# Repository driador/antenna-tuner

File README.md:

# 1500 W Automated Antenna Tuner

KF0OWR's homebuilt 1500 W remote balanced tuner for a doublet on 160–10 m. It uses a 34 µH
roller inductor, two vacuum capacitors and Tohtsu relays, and sits in a wall-mounted
16 × 16 × 24″ cabinet. The design log is the source of truth. Everything else in this repo
(CAD, drawings, NEC models, KiCad boards) supports it, and the log cites these files by their
repo paths.

## Layout

| Path | Contents |
|---|---|
| `doc/design-log.md` | **Design log** (current revision in its header). §9 is the open-item list; §11 holds superseded designs |
| `doc/design-review-rev3.2.md` | Independent design review of Rev 3.2 and its dispositions |
| `doc/vacuum-cap-testing.md` | Bench procedure for the used vacuum capacitors |
| `doc/bench-tests.md` | Bench tests that retire the build risks before the enclosure is cut: the roller (L, idle-turn resonance, torque, contact heat, Q), K1 and K2 at full power, the AD8302 sign probe, and the 160 m decision if Q is low |
| `doc/diagrams/` | Graphviz sources (`*.dot`) and the rendered SVGs the log embeds |
| `doc/*.pdf` | Built log and review PDFs, plus a reference worksheet |
| `cad/` | build123d models (roller, enclosure, harness) and FreeCAD TechDraw sheet generators |
| `cad/out/*.pdf` | Drawing sheets: `L-100…109` roller, `E-200…219` enclosure, populated cabinet and harness |
| `nec/` | nec2++ and Python analyses: capacitor and inductor demand, roller and choke sweeps, tuning time, the general rating |
| `nec/out/*.csv`, `*.txt` | Analysis summaries the log quotes |
| `nec/data/` | Fair-Rite #61 material data (complex permeability, Pv vs B); Fair-Rite's, not under the project licenses |
| `kicad/` | Control and measurement boards, generated from Python (schematic → netlist → PCB → freerouting → DRC, `route.sh`); fab zip from `fab.sh` |
| `fw/` | Firmware: the portable C++17 core (tuning state machine, solver, bridge math, fault policy, motion planning) with its closed-loop host tests, and the Teensy 4.1 layer (PlatformIO); see `fw/README.md` |
| `host/` | The bench PC's tools: the CAT bridge (band-follow and one-button tune through Hamlib or flrig) and the firmware update over the network; see `host/README.md` |
| `LICENSE`, `NOTICE` | The CERN-OHL-W v2 text for the hardware and design; what each license covers, the notices and the third-party files (the firmware's GPL text is `fw/LICENSE`) |
| `archive/` | Early drafts and the Rev 3.3 / 3.4 log snapshots the log cites |

## Toolchain

| Area | Needs |
|---|---|
| Log / review PDF | `pandoc`, `weasyprint`, `poppler` (`pdftocairo`, `pdfinfo`), `python3`; `graphviz` only to re-render a diagram |
| CAD | Python 3.12 venv with `cad/requirements.txt` (build123d 0.13); FreeCAD 1.1 plus `xvfb-run` for the sheets |
| NEC | `nec2++` built statically at `~/src/necpp/build/src/nec2++` (scripts call that path); Python 3 stdlib only |
| KiCad | KiCad 10 (`kicad-cli`, `pcbnew` Python module), Java 25 and freerouting (`kicad/route.sh`) |
| Firmware | CMake ≥ 3.16 and a C++17 compiler for the host build and tests; PlatformIO for the Teensy build (it fetches PJRC's ARM toolchain and the QNEthernet library); `python3` to regenerate its tables |

Set up the CAD environment:

```bash
uv venv cad/.venv --python 3.12
uv pip install --python cad/.venv/bin/python -r cad/requirements.txt
```

Build `nec2++` (the shared-library build breaks once `libnecpp.so` goes missing, so use the static build):

```bash
git clone https://github.com/tmolteno/necpp ~/src/necpp
cmake -S ~/src/necpp -B ~/src/necpp/build -DBUILD_SHARED_LIBS=OFF -DCMAKE_BUILD_TYPE=Release
cmake --build ~/src/necpp/build -j
```

## Build order

When the geometry changes, regenerate the CAD and sheets **in this order**, then rebuild the log
so appendices A/B pick up the new sheets:

```bash
cd cad
.venv/bin/python roller.py          # roller model + interference check
.venv/bin/python enclosure.py       # cabinet, panels, fixtures + interference check
.venv/bin/python harness.py         # color-coded wire runs + clearance check
.venv/bin/python svgviews.py        # hidden-line SVG views used by the sheets
timeout 900 xvfb-run -a freecad drawings.py             # L-100…109
timeout 900 xvfb-run -a freecad drawings_enclosure.py   # E-200…219
cd ../doc && ./build.sh             # → doc/tuner-design-log.pdf
```

The panel sheets place each cutout by ordinates from the panel's lower-left corner and label it with its
size. `cad/ordinate.py` lays these out as an SVG overlay on each view, and it needs no FreeCAD:
`python3 ordinate.py /tmp/out` writes every panel's overlay, so a layout can be checked quickly.

Always wrap the FreeCAD runs in `timeout`. A module-level exception in a sheet script leaves
FreeCAD hanging under xvfb with an empty log. Re-render a diagram with
`dot -Tsvg doc/diagrams/X.dot -o doc/diagrams/X.svg`. The review builds with `doc/build_review.sh`.

## What is tracked

- **Git LFS** (`.gitattributes`) holds every `*.pdf`, `*.png` and `*.jpg`: drawing sheets, built
  PDFs, KiCad plots and references. Run `git lfs install --local` after cloning.
- **Not tracked** (`.gitignore`) are outputs the scripts regenerate wholesale on every run:
  - STEP models and FreeCAD documents
  - sheet SVGs and logs in `cad/out/`
  - raw NEC decks and solver output (`nec/out/*.nec`, `*.out`, about 420 MB)
  - the HTML intermediates and `doc/sheets/`
  - the firmware builds, `fw/build/` and `fw/.pio/`
  - the venv
  - `.*.pre-*` working backups, since git history replaces them
- The summaries that analyses produce (`nec/out/*.csv`, `*.txt`, `nec/cap_demand_rev37b.out`)
  **are** tracked, because the log quotes them.

## License

This is open hardware. The boards, CAD, drawings, NEC models and the design log are licensed under
the [CERN-OHL-W v2](LICENSE), and the firmware in `fw/` and the bench PC's tools in `host/` under
the [GPL v3 or later](fw/LICENSE). [`NOTICE`](NOTICE) has the details, including
the third-party files. Source location: <https://github.com/driador/antenna-tuner>.

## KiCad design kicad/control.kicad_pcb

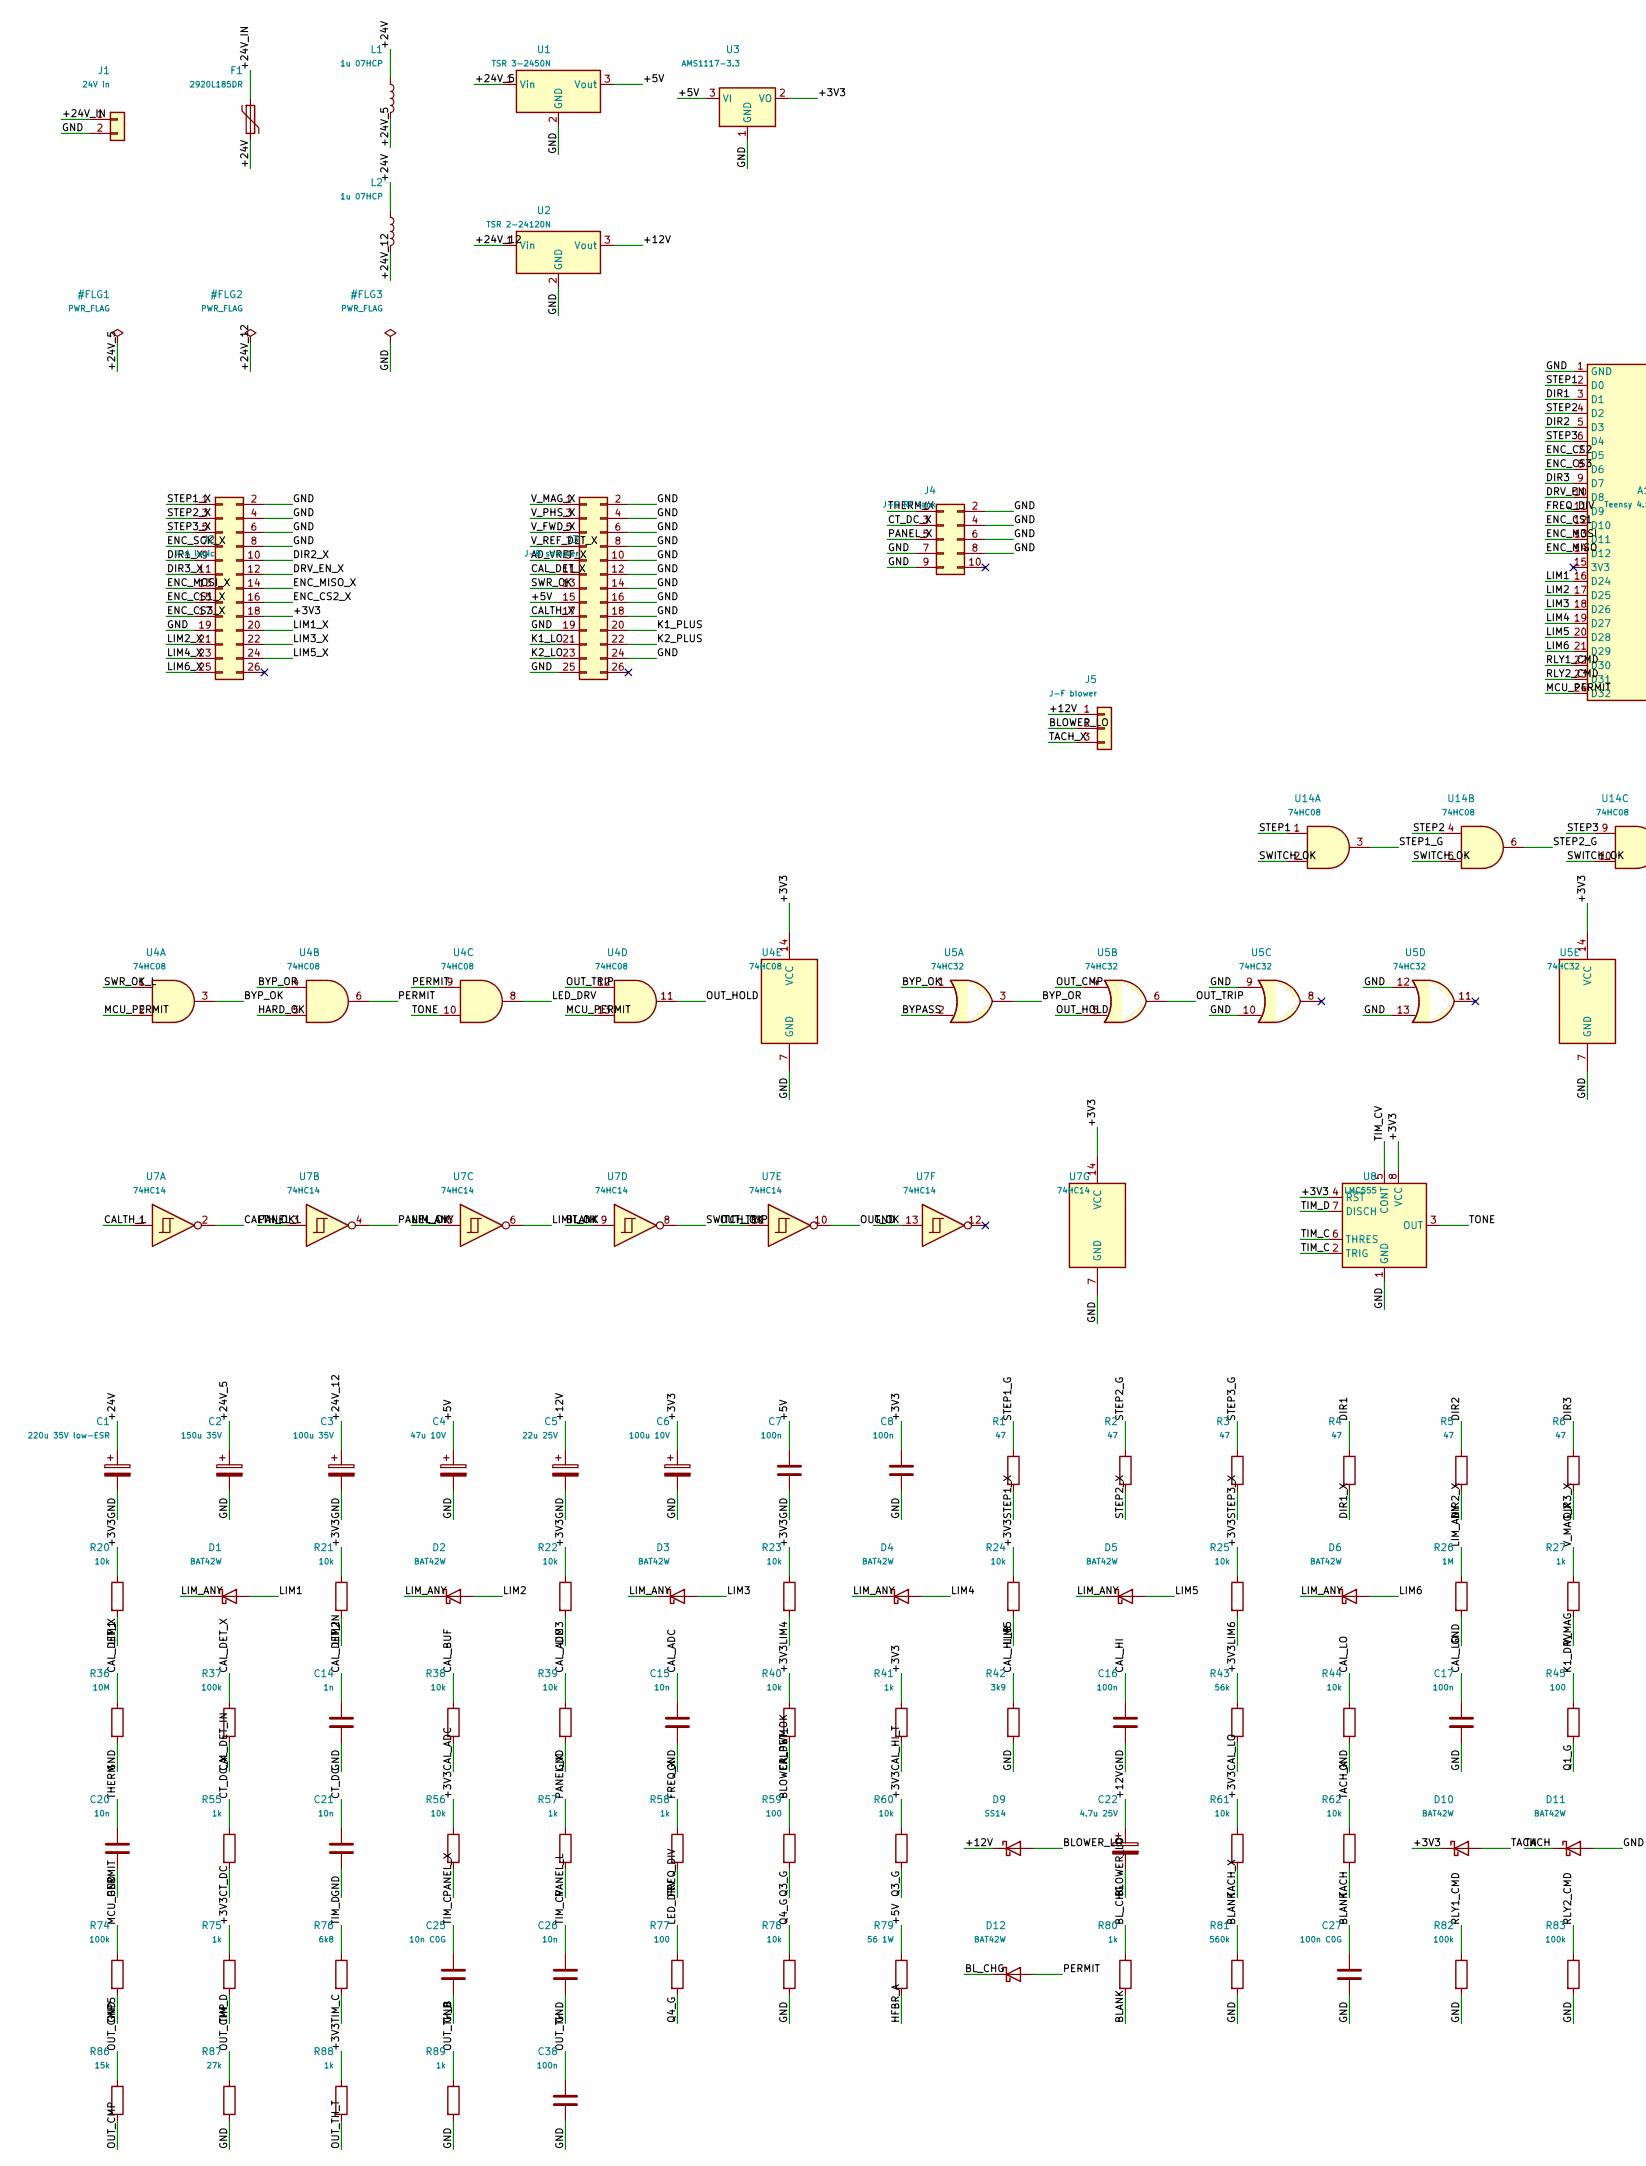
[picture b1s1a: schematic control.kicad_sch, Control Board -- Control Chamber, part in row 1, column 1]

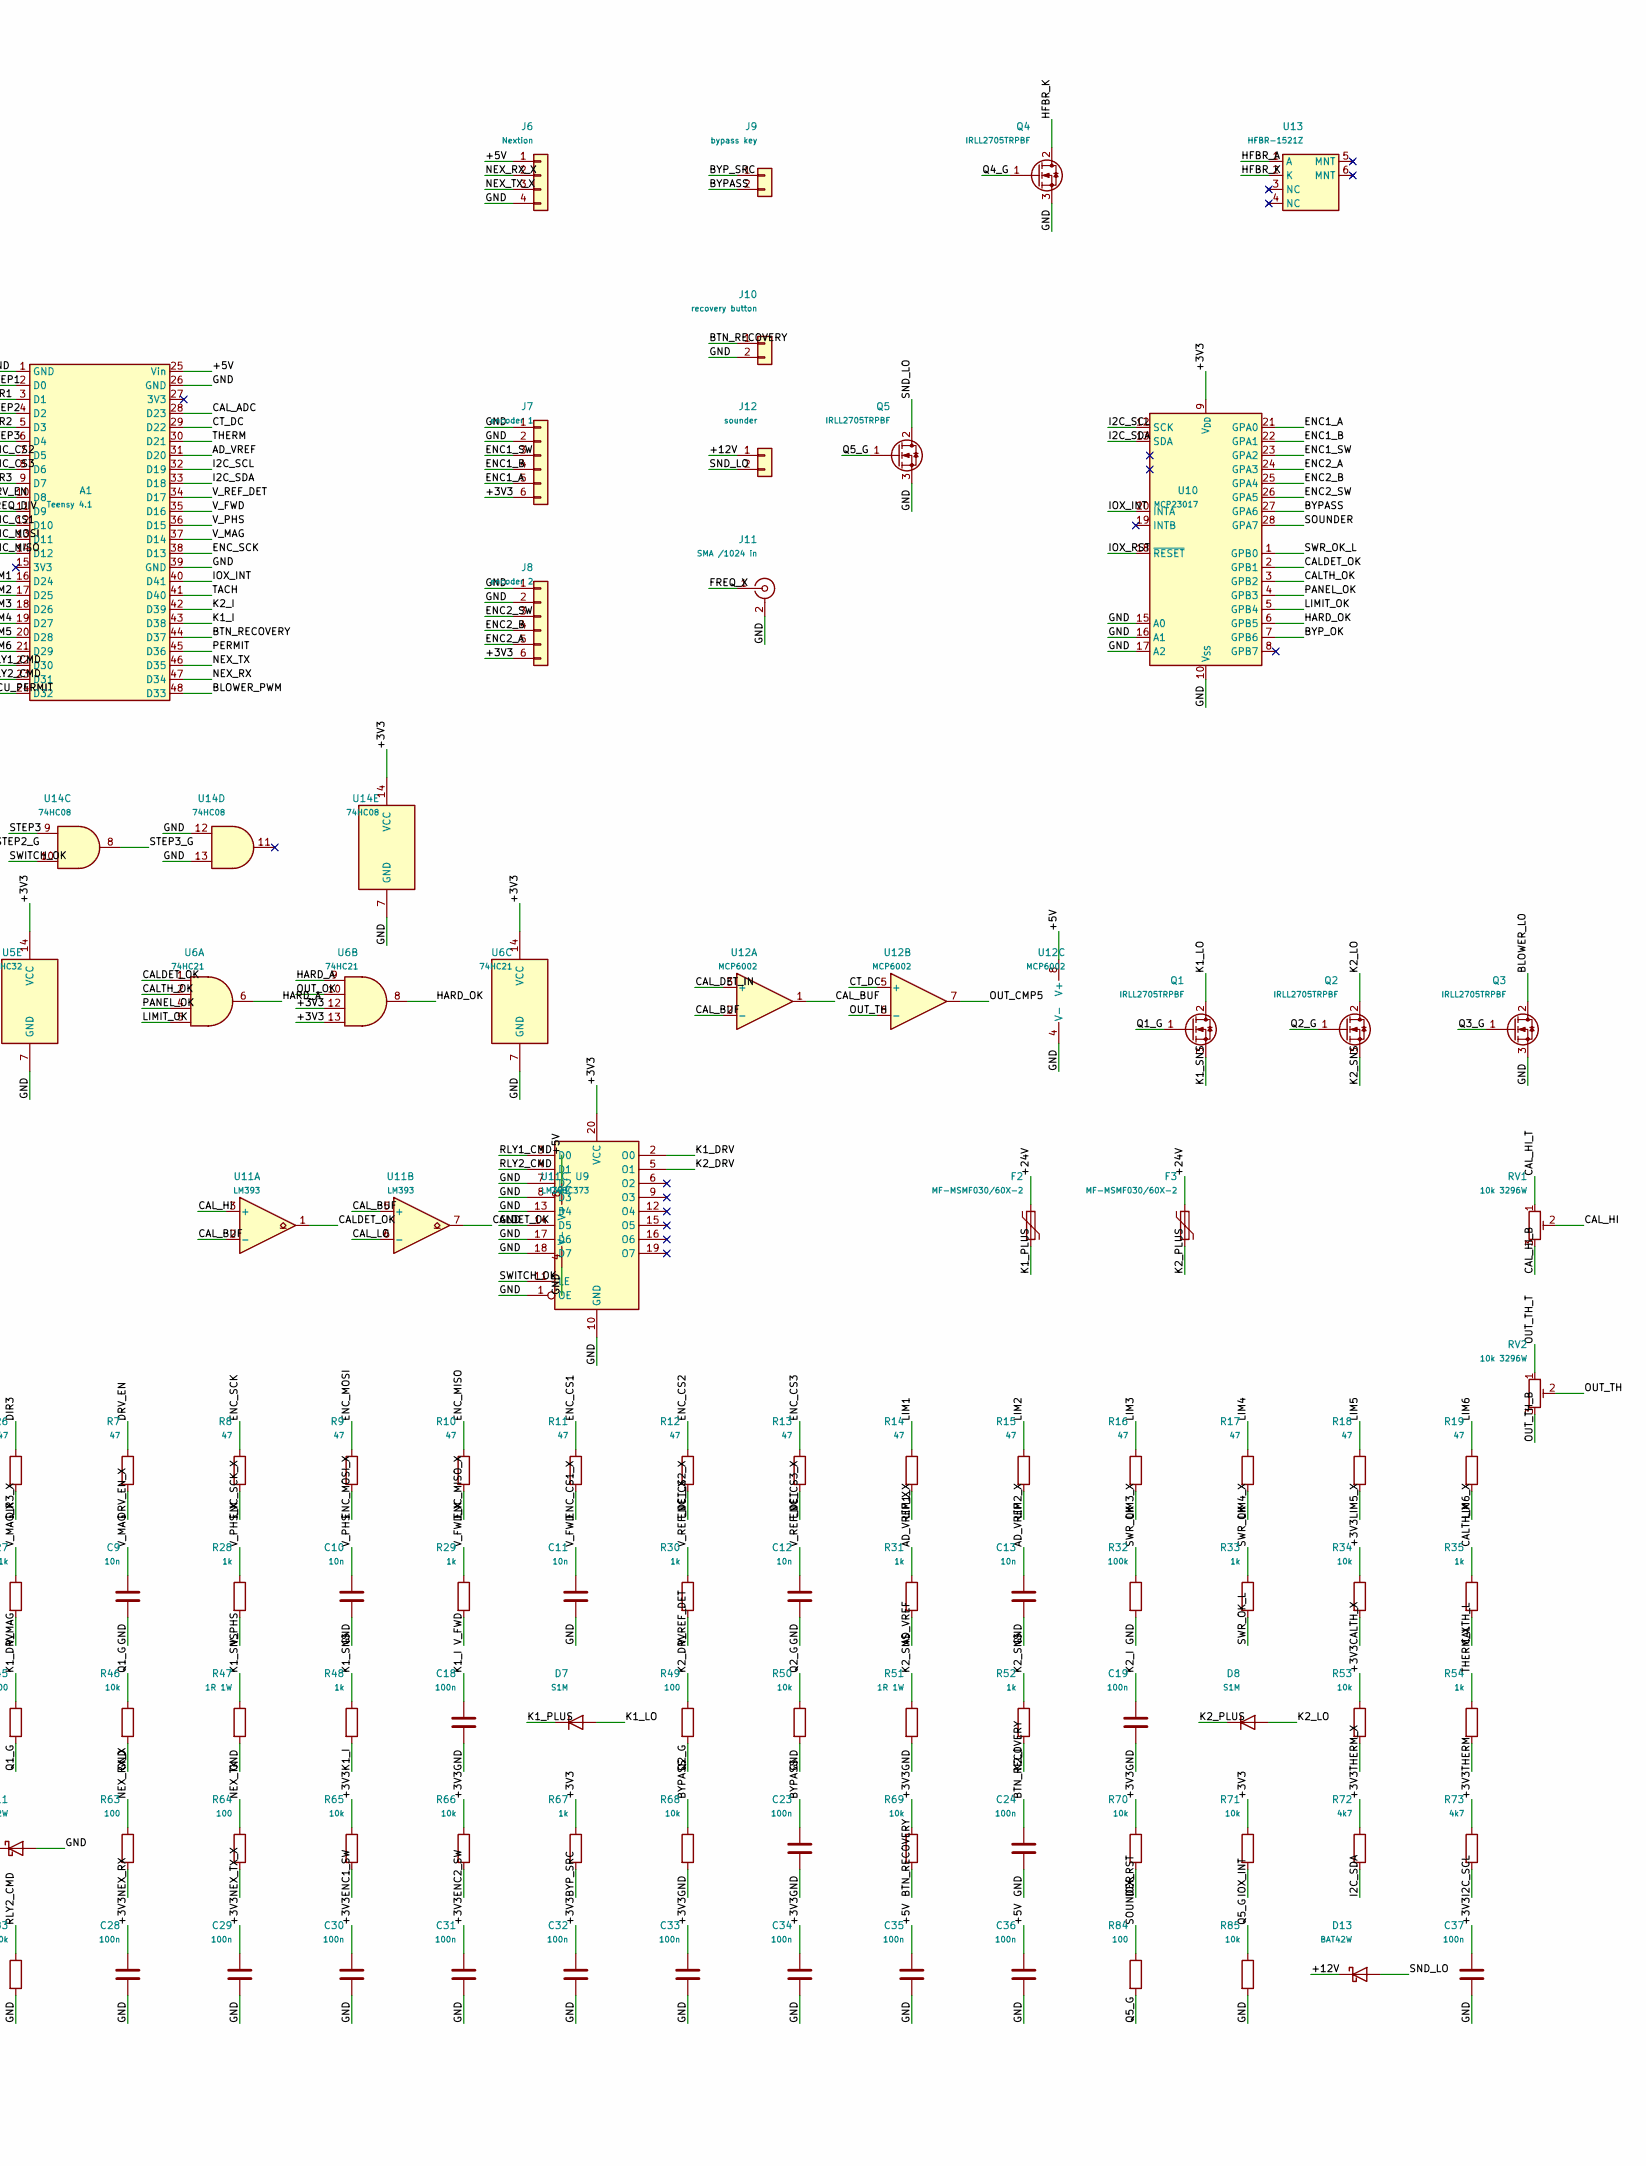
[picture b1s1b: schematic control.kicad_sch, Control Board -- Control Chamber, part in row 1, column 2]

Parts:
A1: Teensy 4.1; Teensy4.1
C1: 220u 35V low-ESR; CP_Radial_D8.0mm_P3.50mm
C2: 150u 35V; CP_Radial_D8.0mm_P3.50mm
C3: 100u 35V; CP_Radial_D6.3mm_P2.50mm
C4: 47u 10V; CP_Radial_D5.0mm_P2.50mm
C5: 22u 25V; CP_Radial_D5.0mm_P2.50mm
C6: 100u 10V; CP_Radial_D6.3mm_P2.50mm
C7, C8, C16, C17, C18, C19, C23, C24, C28, C29, C30, C31, C32, C33, C34, C35, C36, C37, C38: 100n; C_1206_3216Metric
C9, C10, C11, C12, C13, C15, C20, C21, C26: 10n; C_1206_3216Metric
C14: 1n; C_1206_3216Metric
C22: 4.7u 25V; CP_Radial_D5.0mm_P2.50mm
C25: 10n C0G; C_1206_3216Metric
C27: 100n C0G; C_1206_3216Metric
D1, D2, D3, D4, D5, D6, D10, D11, D12, D13: BAT42W; D_SOD-123
D7, D8: S1M; D_SMA
D9: SS14; D_SMA
F1: 2920L185DR; Fuse_2920_7451Metric
F2, F3: MF-MSMF030/60X-2; Fuse_1812_4532Metric
J1: 24V in; TerminalBlock_Phoenix_MKDS-1,5-2-5.08_1x02_P5.08mm_Horizont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
J2: J-A logic; IDC-Header_2x13_P2.54mm_Vertical
J3: J-B sampler; IDC-Header_2x13_P2.54mm_Vertical
J4: J-E RF tank; IDC-Header_2x05_P2.54mm_Vertical
J5: J-F blower; PinHeader_1x03_P2.54mm_Vertical
J6: Nextion; PinHeader_1x04_P2.54mm_Vertical
J7: encoder 1; PinHeader_1x06_P2.54mm_Vertical
J8: encoder 2; PinHeader_1x06_P2.54mm_Vertical
J9: bypass key; PinHeader_1x02_P2.54mm_Vertical
J10: recovery button; PinHeader_1x02_P2.54mm_Vertical
J11: SMA /1024 in; SMA_Amphenol_132134-11_Vertical
J12: sounder; PinHeader_1x02_P2.54mm_Vertical
L1, L2: 1u 07HCP; L_Radial_D7.8mm_P5.00mm_Fastron_07HCP
Q1, Q2, Q3, Q4, Q5: IRLL2705TRPBF; SOT-223-3_TabPin2
R1, R2, R3, R4, R5, R6, R7, R8, R9, R10, R11, R12, R13, R14, R15, R16, R17, R18, R19: 47; R_1206_3216Metric
R20, R21, R22, R23, R24, R25, R34, R38, R39, R40, R44, R46, R50, R53, R56, R60, R61, R62, R65, R66, R68, R69, R70, R71, R78, R85: 10k; R_1206_3216Metric
R26: 1M; R_1206_3216Metric
R27, R28, R29, R30, R31, R33, R35, R41, R48, R52, R54, R55, R57, R58, R67, R75, R80, R88, R89: 1k; R_1206_3216Metric
R32, R37, R74, R82, R83: 100k; R_1206_3216Metric
R36: 10M; R_1206_3216Metric
R42: 3k9; R_1206_3216Metric
R43: 56k; R_1206_3216Metric
R45, R49, R59, R63, R64, R77, R84: 100; R_1206_3216Metric
R47, R51: 1R 1W; R_2512_6332Metric
R72, R73: 4k7; R_1206_3216Metric
R76: 6k8; R_1206_3216Metric
R79: 56 1W; R_2512_6332Metric
R81: 560k; R_1206_3216Metric
R86: 15k; R_1206_3216Metric
R87: 27k; R_1206_3216Metric
RV1, RV2: 10k 3296W; Potentiometer_Bourns_3296W_Vertical
U1: TSR 3-2450N; Converter_DCDC_TRACO_TSR2-24xxN_TSR2-24xxxN_THT
U2: TSR 2-24120N; Converter_DCDC_TRACO_TSR2-24xxN_TSR2-24xxxN_THT
U3: AMS1117-3.3; SOT-223-3_TabPin2
U4, U14: 74HC08; SOIC-14_3.9x8.7mm_P1.27mm
U5: 74HC32; SOIC-14_3.9x8.7mm_P1.27mm
U6: 74HC21; SOIC-14_3.9x8.7mm_P1.27mm
U7: 74HC14; SOIC-14_3.9x8.7mm_P1.27mm
U8: LMC555; SOIC-8_3.9x4.9mm_P1.27mm
U9: 74HC373; SOIC-20W_7.5x12.8mm_P1.27mm
U10: MCP23017; SOIC-28W_7.5x17.9mm_P1.27mm
U11: LM393; SOIC-8_3.9x4.9mm_P1.27mm
U12: MCP6002; SOIC-8_3.9x4.9mm_P1.27mm
U13: HFBR-1521Z; AGILENT_HFBR-152x

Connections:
+3V3: C6.1, C8.1, C28.1, C29.1, C30.1, C31.1, C32.1, C33.1, C34.1, C37.1, D10.1 (K), J2.18, J7.6, J8.6, R20.1, R21.1, R22.1, R23.1, R24.1, R25.1, R34.1, R40.1, R41.1, R43.1, R53.1, R56.1, R60.1, R61.1, R65.1, R66.1, R67.1, R69.1, R70.1, R71.1, R72.1, R73.1, R75.1, R88.1, U3.2 (VO), U4.14 (VCC), U5.14 (VCC), U6.12, U6.13, U6.14 (VCC), U7.14 (VCC), U8.4 (~RST), U8.8 (VCC), U9.20 (VCC), U10.9 (V_{DD}), U14.14 (VCC)
+5V: A1.25 (Vin), C4.1, C7.1, C35.1, C36.1, J3.15, J6.1, R79.1, U1.3 (Vout), U3.3 (VI), U11.8 (V+), U12.8 (V+)
+12V: C5.1, C22.1, D9.1 (K), D13.1 (K), J5.1, J12.1, U2.3 (Vout)
+24V: C1.1, F1.2, F2.1, F3.1, L1.1, L2.1
+24V_5: C2.1, L1.2, U1.1 (Vin)
+24V_12: C3.1, L2.2, U2.1 (Vin)
+24V_IN: F1.1, J1.1
AD_VREF: A1.31 (20), C13.1, R31.2
AD_VREF_X: J3.9, R31.1
BLANK: C27.1, R80.2, R81.1, U7.9
BLOWER_LO: C22.2, D9.2 (A), J5.2, Q3.2 (D)
BLOWER_PWM: A1.48 (33), R59.1
BL_CHG: D12.1 (K), R80.1
BTN_RECOVERY: A1.44 (37), C24.1, J10.1, R69.2
BYPASS: C23.1, J9.2, R68.1, U5.2, U10.27 (GPA6)
BYP_OK: U4.3, U5.1, U10.7 (GPB6)
BYP_OR: U4.4, U5.3
BYP_SRC: J9.1, R67.2
CALDET_OK: R40.2, U6.1, U10.2 (GPB1), U11.1, U11.7
CALTH_L: R35.2, U7.1
CALTH_OK: U6.2, U7.2, U10.3 (GPB2)
CALTH_X: J3.17, R34.2, R35.1
CAL_ADC: A1.28 (23), C15.1, R38.2, R39.1
CAL_BUF: R38.1, U11.2 (-), U11.5 (+), U12.1, U12.2 (-)
CAL_DET_IN: C14.1, R37.2, U12.3 (+)
CAL_DET_X: J3.11, R36.1, R37.1
CAL_HI: C16.1, RV1.2, U11.3 (+)
CAL_HI_B: R42.1, RV1.3
CAL_HI_T: R41.2, RV1.1
CAL_LO: C17.1, R43.2, R44.1, U11.6 (-)
CT_DC: A1.29 (22), C21.1, R55.2, U12.5 (+)
CT_DC_X: J4.3, R55.1
DIR1: A1.3 (1), R4.1
DIR1_X: J2.9, R4.2
DIR2: A1.5 (3), R5.1
DIR2_X: J2.10, R5.2
DIR3: A1.9 (7), R6.1
DIR3_X: J2.11, R6.2
DRV_EN: A1.10 (8), R7.1
DRV_EN_X: J2.12, R7.2
ENC1_A: J7.5, U10.21 (GPA0)
ENC1_B: J7.4, U10.22 (GPA1)
ENC1_SW: J7.3, R65.2, U10.23 (GPA2)
ENC2_A: J8.5, U10.24 (GPA3)
ENC2_B: J8.4, U10.25 (GPA4)
ENC2_SW: J8.3, R66.2, U10.26 (GPA5)
ENC_CS1: A1.12 (10), R11.1
ENC_CS1_X: J2.15, R11.2
ENC_CS2: A1.7 (5), R12.1
ENC_CS2_X: J2.16, R12.2
ENC_CS3: A1.8 (6), R13.1
ENC_CS3_X: J2.17, R13.2
ENC_MISO: A1.14 (12), R10.1
ENC_MISO_X: J2.14, R10.2
ENC_MOSI: A1.13 (11), R9.1
ENC_MOSI_X: J2.13, R9.2
ENC_SCK: A1.38 (13), R8.1
ENC_SCK_X: J2.7, R8.2
FREQ_DIV: A1.11 (9), R58.2
FREQ_X: J11.1 (In), R58.1
GND: A1.1 (GND), A1.26 (GND), A1.39 (GND), C1.2, C2.2, C3.2, C4.2, C5.2, C6.2, C7.2, C8.2, C9.2, C10.2, C11.2, C12.2, C13.2, C14.2, C15.2, C16.2, C17.2, C18.2, C19.2, C20.2, C21.2, C23.2, C24.2, C25.2, C26.2, C27.2, C28.2, C29.2, C30.2, C31.2, C32.2, C33.2, C34.2, C35.2, C36.2, C37.2, C38.2, D11.2 (A), J1.2, J2.2, J2.4, J2.6, J2.8, J2.19, J3.2, J3.4, J3.6, J3.8, J3.10, J3.12, J3.14, J3.16, J3.18, J3.19, J3.24, J3.25, J4.2, J4.4, J4.6, J4.7, J4.8, J4.9, J6.4, J7.1, J7.2, J8.1, J8.2, J10.2, J11.2 (Ext), Q3.3 (S), Q4.3 (S), Q5.3 (S), R26.2, R32.2, R36.2, R39.2, R42.2, R44.2, R46.2, R47.2, R50.2, R51.2, R68.2, R74.2, R78.2, R81.2, R82.2, R83.2, R85.2, R87.2, R89.2, U1.2 (GND), U2.2 (GND), U3.1 (GND), U4.7 (GND), U5.7 (GND), U5.9, U5.10, U5.12, U5.13, U6.7 (GND), U7.7 (GND), U7.13, U8.1 (GND), U9.1 (OE), U9.7 (D2), U9.8 (D3), U9.10 (GND), U9.13 (D4), U9.14 (D5), U9.17 (D6), U9.18 (D7), U10.10 (V_{SS}), U10.15 (A0), U10.16 (A1), U10.17 (A2), U11.4 (V-), U12.4 (V-), U14.7 (GND), U14.12, U14.13
HARD_A: U6.6, U6.9
HARD_OK: U4.5, U6.8, U10.6 (GPB5)
HFBR_A: R79.2, U13.1 (A)
HFBR_K: Q4.2 (D), U13.2 (K)
I2C_SCL: A1.32 (19), R73.2, U10.12 (SCK)
I2C_SDA: A1.33 (18), R72.2, U10.13 (SDA)
IOX_INT: A1.40 (41), R71.2, U10.20 (INTA)
IOX_RST: R70.2, U10.18 (~RESET)
K1_DRV: R45.1, U9.2 (O0)
K1_I: A1.43 (38), C18.1, R48.2
K1_LO: D7.2 (A), J3.21, Q1.2 (D)
K1_PLUS: D7.1 (K), F2.2, J3.20
K1_SNS: Q1.3 (S), R47.1, R48.1
K2_DRV: R49.1, U9.5 (O1)
K2_I: A1.42 (39), C19.1, R52.2
K2_LO: D8.2 (A), J3.23, Q2.2 (D)
K2_PLUS: D8.1 (K), F3.2, J3.22
K2_SNS: Q2.3 (S), R51.1, R52.1
LED_DRV: R77.1, U4.8
LIM1: A1.16 (24), D1.2 (A), R14.1, R20.2
LIM1_X: J2.20, R14.2
LIM2: A1.17 (25), D2.2 (A), R15.1, R21.2
LIM2_X: J2.21, R15.2
LIM3: A1.18 (26), D3.2 (A), R16.1, R22.2
LIM3_X: J2.22, R16.2
LIM4: A1.19 (27), D4.2 (A), R17.1, R23.2
LIM4_X: J2.23, R17.2
LIM5: A1.20 (28), D5.2 (A), R18.1, R24.2
LIM5_X: J2.24, R18.2
LIM6: A1.21 (29), D6.2 (A), R19.1, R25.2
LIM6_X: J2.25, R19.2
LIMIT_OK: U6.5, U7.6, U10.5 (GPB4)
LIM_ANY: D1.1 (K), D2.1 (K), D3.1 (K), D4.1 (K), D5.1 (K), D6.1 (K), R26.1, U7.5
MCU_PERMIT: A1.24 (32), R74.1, U4.2, U4.13
NEX_RX: A1.47 (34), R63.2
NEX_RX_X: J6.2, R63.1
NEX_TX: A1.46 (35), R64.1
NEX_TX_X: J6.3, R64.2
OUT_CMP: R86.2, R87.1, U5.4
OUT_CMP5: R86.1, U12.7
OUT_HOLD: U4.11, U5.5
OUT_OK: U6.10, U7.10
OUT_TH: C38.1, RV2.2, U12.6 (-)
OUT_TH_B: R89.1, RV2.3
OUT_TH_T: R88.2, RV2.1
OUT_TRIP: U4.12, U5.6, U7.11
PANEL_L: R57.2, U7.3
PANEL_OK: U6.4, U7.4, U10.4 (GPB3)
PANEL_X: J4.5, R56.2, R57.1
PERMIT: A1.45 (36), D12.2 (A), U4.6, U4.9
Q1_G: Q1.1 (G), R45.2, R46.1
Q2_G: Q2.1 (G), R49.2, R50.1
Q3_G: Q3.1 (G), R59.2, R60.2
Q4_G: Q4.1 (G), R77.2, R78.1
Q5_G: Q5.1 (G), R84.2, R85.1
RLY1_CMD: A1.22 (30), R82.1, U9.3 (D0)
RLY2_CMD: A1.23 (31), R83.1, U9.4 (D1)
SND_LO: D13.2 (A), J12.2, Q5.2 (D)
SOUNDER: R84.1, U10.28 (GPA7)
STEP1: A1.2 (0), U14.1
STEP1_G: R1.1, U14.3
STEP1_X: J2.1, R1.2
STEP2: A1.4 (2), U14.4
STEP2_G: R2.1, U14.6
STEP2_X: J2.3, R2.2
STEP3: A1.6 (4), U14.9
STEP3_G: R3.1, U14.8
STEP3_X: J2.5, R3.2
SWITCH_OK: U7.8, U9.11 (LE), U14.2, U14.5, U14.10
SWR_OK: J3.13, R32.1, R33.1
SWR_OK_L: R33.2, U4.1, U10.1 (GPB0)
TACH: A1.41 (40), D10.2 (A), D11.1 (K), R62.2
TACH_X: J5.3, R61.2, R62.1
THERM: A1.30 (21), C20.1, R54.2
THERM_X: J4.1, R53.2, R54.1
TIM_C: C25.1, R76.2, U8.2 (TRIG), U8.6 (THRES)
TIM_CV: C26.1, U8.5 (CONT)
TIM_D: R75.2, R76.1, U8.7 (DISCH)
TONE: U4.10, U8.3 (OUT)
V_FWD: A1.35 (16), C11.1, R29.2
V_FWD_X: J3.5, R29.1
V_MAG: A1.37 (14), C9.1, R27.2
V_MAG_X: J3.1, R27.1
V_PHS: A1.36 (15), C10.1, R28.2
V_PHS_X: J3.3, R28.1
V_REF_DET: A1.34 (17), C12.1, R30.2
V_REF_DET_X: J3.7, R30.1

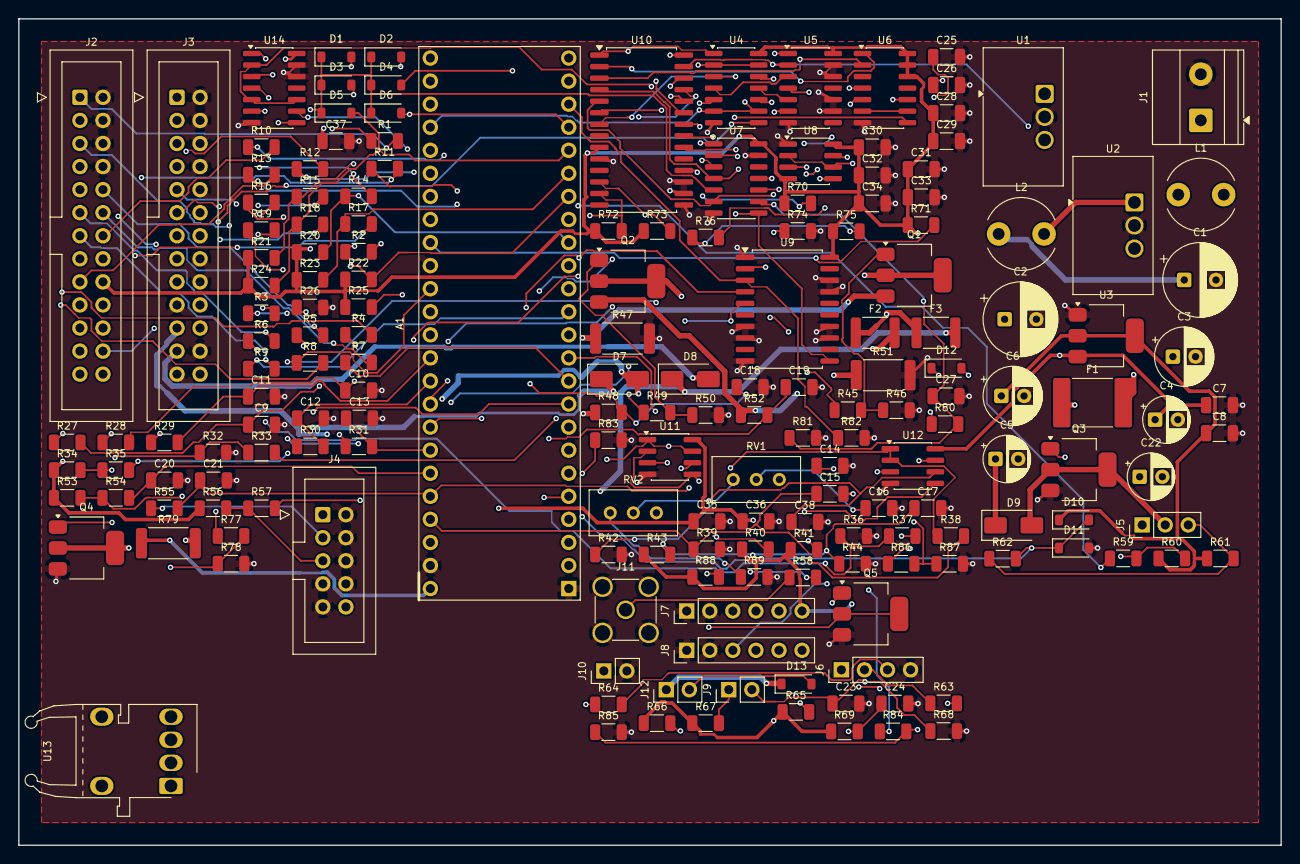
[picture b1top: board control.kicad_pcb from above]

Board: 4 copper layers, 139.0 x 91.0 mm, 179 parts (0 on the bottom side), 148 nets.

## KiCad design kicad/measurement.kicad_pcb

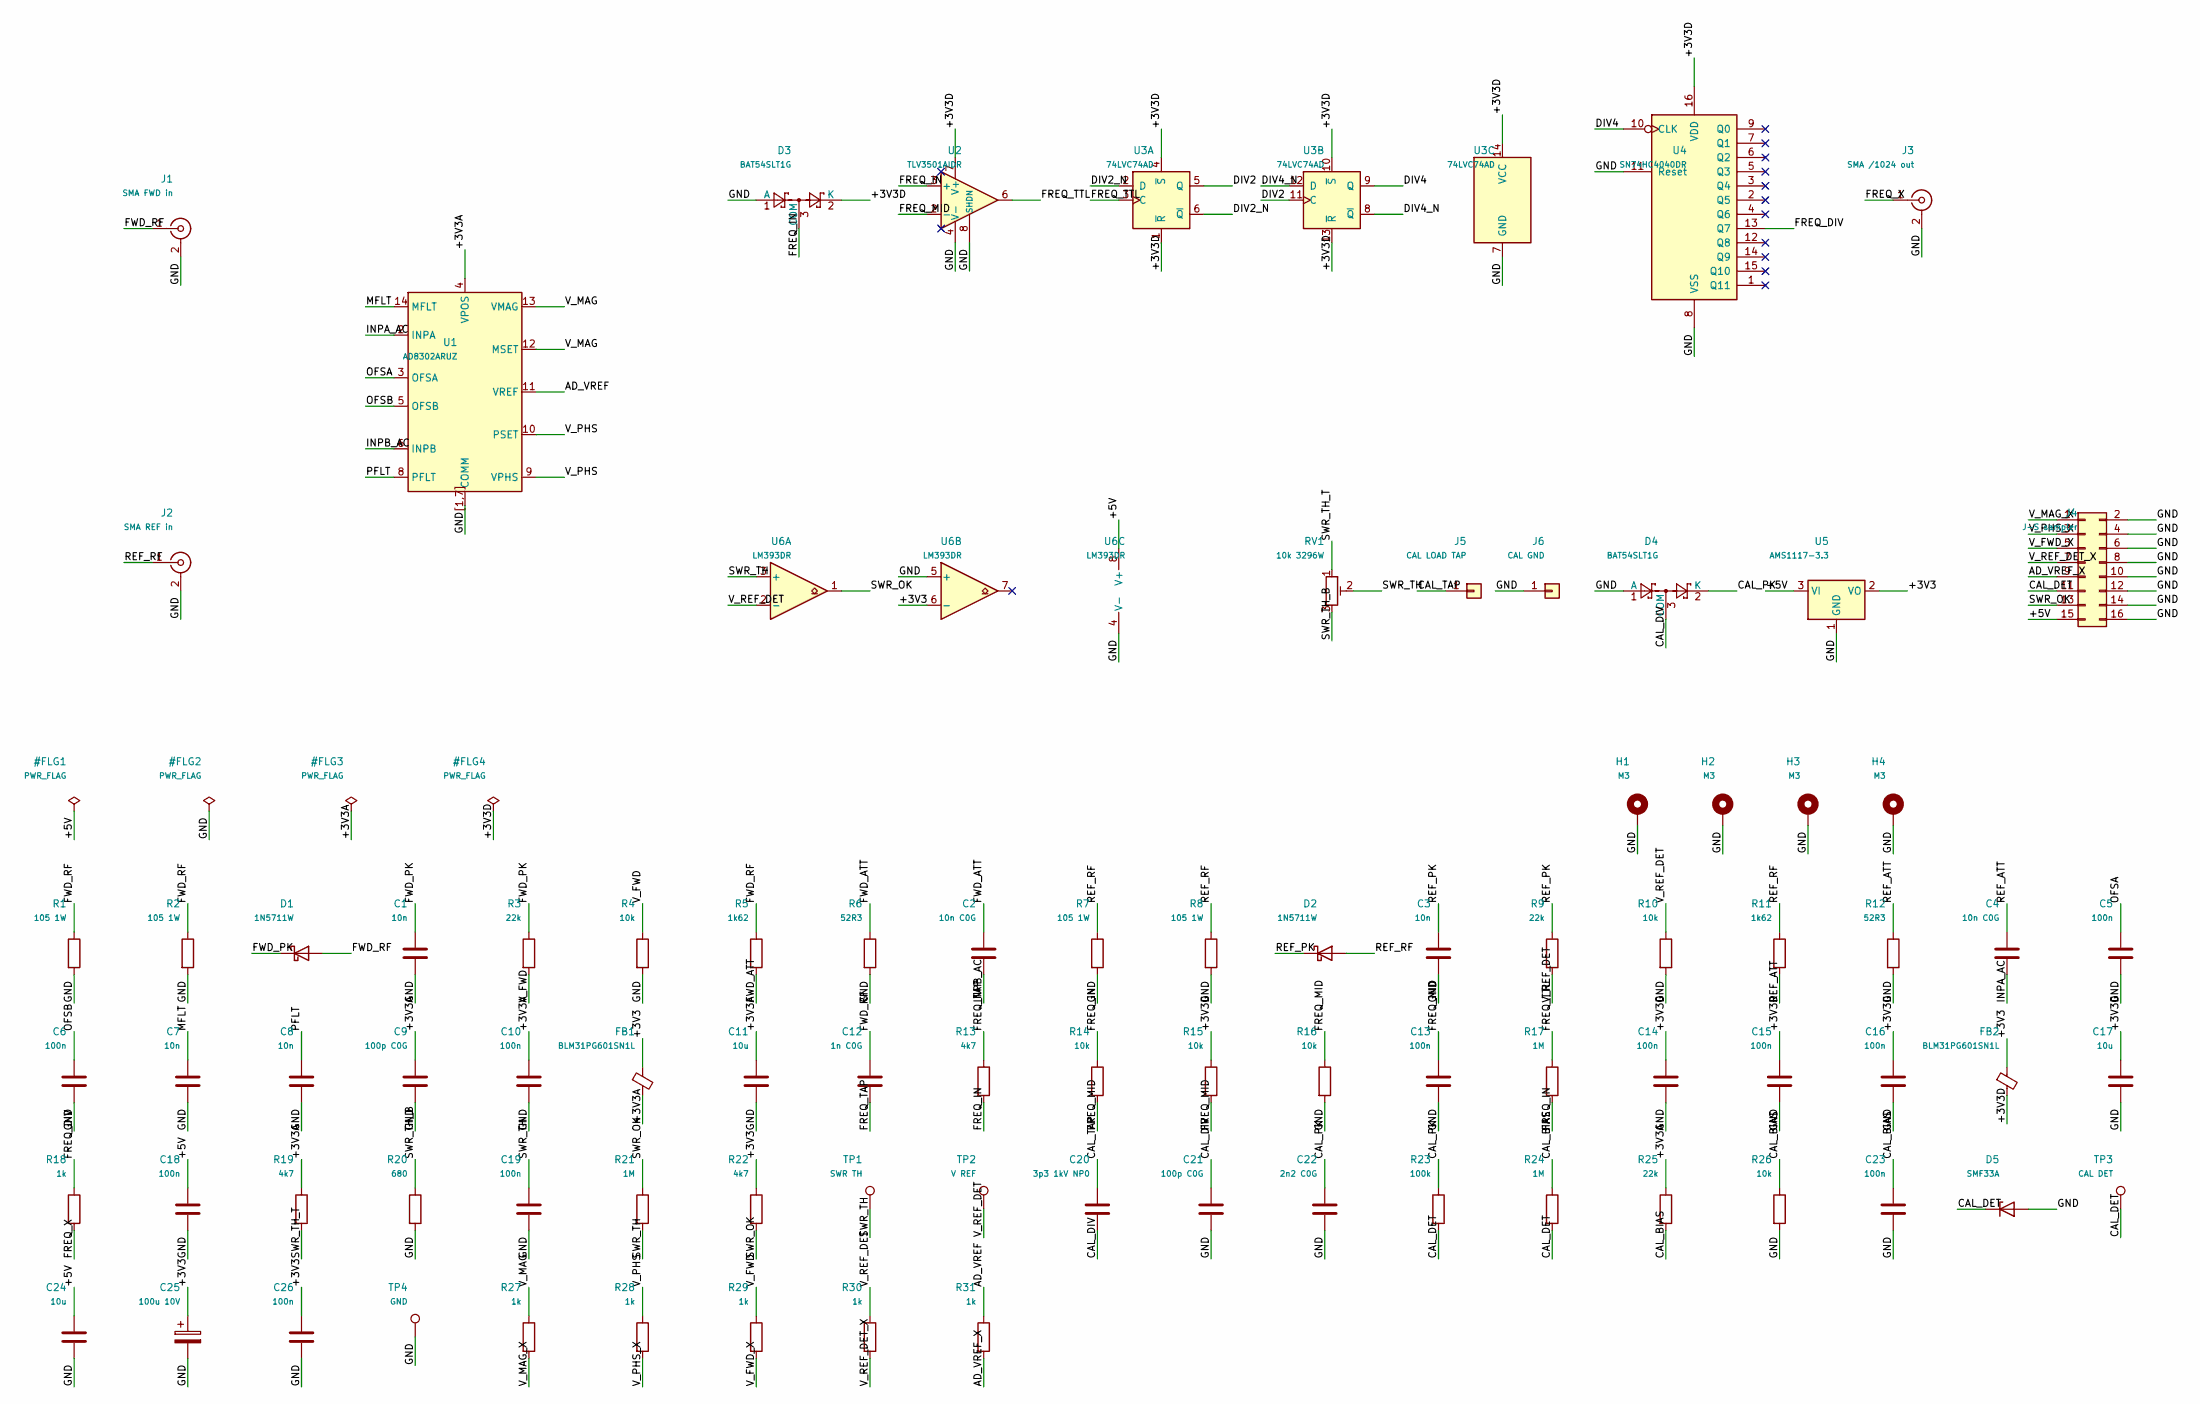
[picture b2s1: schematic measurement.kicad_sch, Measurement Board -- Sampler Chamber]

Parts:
C1, C3, C7, C8: 10n; C_1206_3216Metric
C2, C4: 10n C0G; C_1206_3216Metric
C5, C6, C10, C13, C14, C15, C16, C18, C19, C23, C26: 100n; C_1206_3216Metric
C9, C21: 100p C0G; C_1206_3216Metric
C11, C17, C24: 10u; C_1206_3216Metric
C12: 1n C0G; C_1206_3216Metric
C20: 3p3 1kV NP0; C_Disc_D7.5mm_W5.0mm_P5.00mm
C22: 2n2 C0G; C_1206_3216Metric
C25: 100u 10V; CP_Radial_D6.3mm_P2.50mm
D1, D2: 1N5711W; D_SOD-123
D3, D4: BAT54SLT1G; SOT-23
D5: SMF33A; D_SOD-123F
FB1, FB2: BLM31PG601SN1L; L_1206_3216Metric
H1, H2, H3, H4: M3; MountingHole_3.2mm_M3_Pad_Via
J1: SMA FWD in; SMA_Molex_73251-1153_EdgeMount_Horizontal
J2: SMA REF in; SMA_Molex_73251-1153_EdgeMount_Horizontal
J3: SMA /1024 out; SMA_Molex_73251-1153_EdgeMount_Horizontal
J4: J-S sampler; IDC-Header_2x08_P2.54mm_Vertical
J5: CAL LOAD TAP; TestPoint_THTPad_D2.5mm_Drill1.2mm
J6: CAL GND; TestPoint_THTPad_D2.5mm_Drill1.2mm
R1, R2, R7, R8: 105 1W; R_2512_6332Metric
R3, R9, R25: 22k; R_1206_3216Metric
R4, R10, R14, R15, R16, R26: 10k; R_1206_3216Metric
R5, R11: 1k62; R_1206_3216Metric
R6, R12: 52R3; R_1206_3216Metric
R13, R19, R22: 4k7; R_1206_3216Metric
R17, R21, R24: 1M; R_1206_3216Metric
R18, R27, R28, R29, R30, R31: 1k; R_1206_3216Metric
R20: 680; R_1206_3216Metric
R23: 100k; R_1206_3216Metric
RV1: 10k 3296W; Potentiometer_Bourns_3296W_Vertical
TP1: SWR TH; TestPoint_THTPad_D1.5mm_Drill0.7mm
TP2: V REF; TestPoint_THTPad_D1.5mm_Drill0.7mm
TP3: CAL DET; TestPoint_THTPad_D1.5mm_Drill0.7mm
TP4: GND; TestPoint_THTPad_D1.5mm_Drill0.7mm
U1: AD8302ARUZ; TSSOP-14_4.4x5mm_P0.65mm
U2: TLV3501AIDR; SOIC-8_3.9x4.9mm_P1.27mm
U3: 74LVC74AD; SOIC-14_3.9x8.7mm_P1.27mm
U4: SN74HC4040DR; SOIC-16_3.9x9.9mm_P1.27mm
U5: AMS1117-3.3; SOT-223-3_TabPin2
U6: LM393DR; SOIC-8_3.9x4.9mm_P1.27mm

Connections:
+3V3: C25.1, C26.1, FB1.1, FB2.1, R22.1, U5.2 (VO), U6.6 (-)
+3V3A: C9.1, C10.1, C11.1, FB1.2, R19.1, R25.1, U1.4 (VPOS)
+3V3D: C14.1, C15.1, C16.1, C17.1, D3.2 (K), FB2.2, R15.1, U2.7 (V+), U3.1 (~R), U3.4 (~S), U3.10 (~S), U3.13 (~R), U3.14 (VCC), U4.16 (VDD)
+5V: C18.1, C24.1, J4.15, U5.3 (VI), U6.8 (V+)
AD_VREF: R31.1, U1.11 (VREF)
AD_VREF_X: J4.9, R31.2
CAL_BIAS: C23.1, R24.1, R25.2, R26.1
CAL_DET: D5.1 (K), J4.11, R23.2, R24.2, TP3.1
CAL_DIV: C20.2, C21.1, D4.3 (COM)
CAL_PK: C22.1, D4.2 (K), R23.1
CAL_TAP: C20.1, J5.1
DIV2: U3.5 (Q), U3.11 (C)
DIV2_N: U3.2 (D), U3.6 (~Q)
DIV4: U3.9 (Q), U4.10 (CLK)
DIV4_N: U3.8 (~Q), U3.12 (D)
FREQ_DIV: R18.1, U4.13 (Q7)
FREQ_IN: D3.3 (COM), R13.2, R14.1, R17.2, U2.3 (+)
FREQ_MID: C13.1, R14.2, R15.2, R16.1, U2.2 (-)
FREQ_TAP: C12.2, R13.1
FREQ_TTL: R17.1, U2.6, U3.3 (C)
FREQ_X: J3.1 (In), R18.2
FWD_ATT: C2.1, R5.2, R6.1
FWD_PK: C1.1, D1.1 (K), R3.1
FWD_RF: C12.1, D1.2 (A), J1.1 (In), R1.1, R2.1, R5.1
GND: C1.2, C3.2, C5.2, C6.2, C7.2, C8.2, C9.2, C10.2, C11.2, C13.2, C14.2, C15.2, C16.2, C17.2, C18.2, C19.2, C21.2, C22.2, C23.2, C24.2, C25.2, C26.2, D3.1 (A), D4.1 (A), D5.2 (A), H1.1, H2.1, H3.1, H4.1, J1.2 (Ext), J2.2 (Ext), J3.2 (Ext), J4.2, J4.4, J4.6, J4.8, J4.10, J4.12, J4.14, J4.16, J6.1, R1.2, R2.2, R4.2, R6.2, R7.2, R8.2, R10.2, R12.2, R16.2, R20.2, R26.2, TP4.1, U1.1, U1.7, U1.[1,7] (COMM), U2.4 (V-), U2.8 (SHDN), U3.7 (GND), U4.8 (VSS), U4.11 (Reset), U5.1 (GND), U6.4 (V-), U6.5 (+)
INPA_AC: C4.2, U1.2 (INPA)
INPB_AC: C2.2, U1.6 (INPB)
MFLT: C7.1, U1.14 (MFLT)
OFSA: C5.1, U1.3 (OFSA)
OFSB: C6.1, U1.5 (OFSB)
PFLT: C8.1, U1.8 (PFLT)
REF_ATT: C4.1, R11.2, R12.1
REF_PK: C3.1, D2.1 (K), R9.1
REF_RF: D2.2 (A), J2.1 (In), R7.1, R8.1, R11.1
SWR_OK: J4.13, R21.1, R22.2, U6.1
SWR_TH: C19.1, R21.2, RV1.2, TP1.1, U6.3 (+)
SWR_TH_B: R20.1, RV1.3
SWR_TH_T: R19.2, RV1.1
V_FWD: R3.2, R4.1, R29.1
V_FWD_X: J4.5, R29.2
V_MAG: R27.1, U1.12 (MSET), U1.13 (VMAG)
V_MAG_X: J4.1, R27.2
V_PHS: R28.1, U1.9 (VPHS), U1.10 (PSET)
V_PHS_X: J4.3, R28.2
V_REF_DET: R9.2, R10.1, R30.1, TP2.1, U6.2 (-)
V_REF_DET_X: J4.7, R30.2

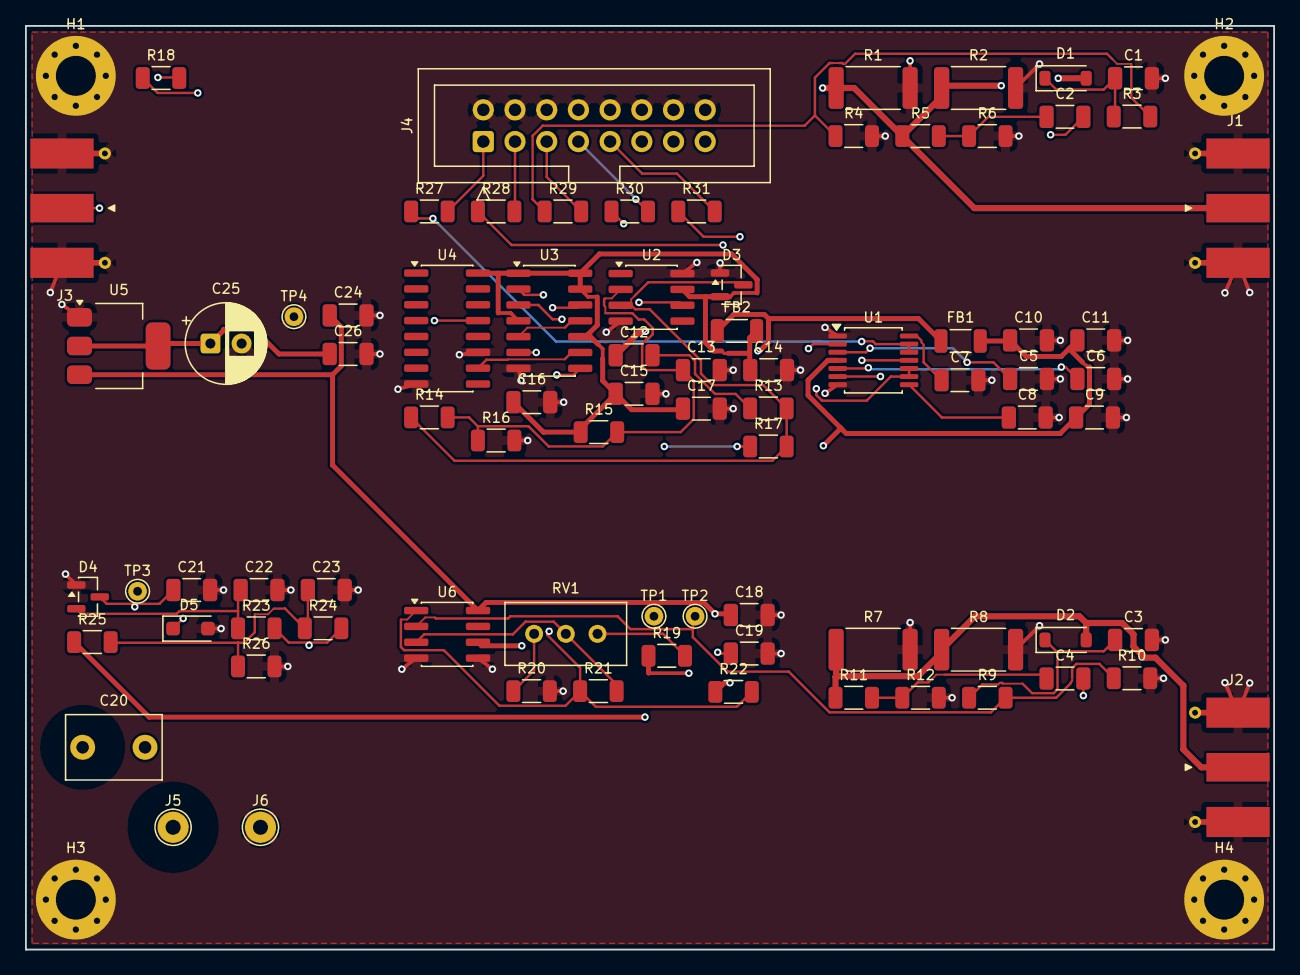
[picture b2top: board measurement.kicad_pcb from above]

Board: 4 copper layers, 100.0 x 74.0 mm, 85 parts (0 on the bottom side), 46 nets.

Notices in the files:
kicad/control.kicad_pcb:
CERN-OHL-W-2.0
kicad/control.kicad_sch:
CERN-OHL-W-2.0  github.com/driador/antenna-tuner
